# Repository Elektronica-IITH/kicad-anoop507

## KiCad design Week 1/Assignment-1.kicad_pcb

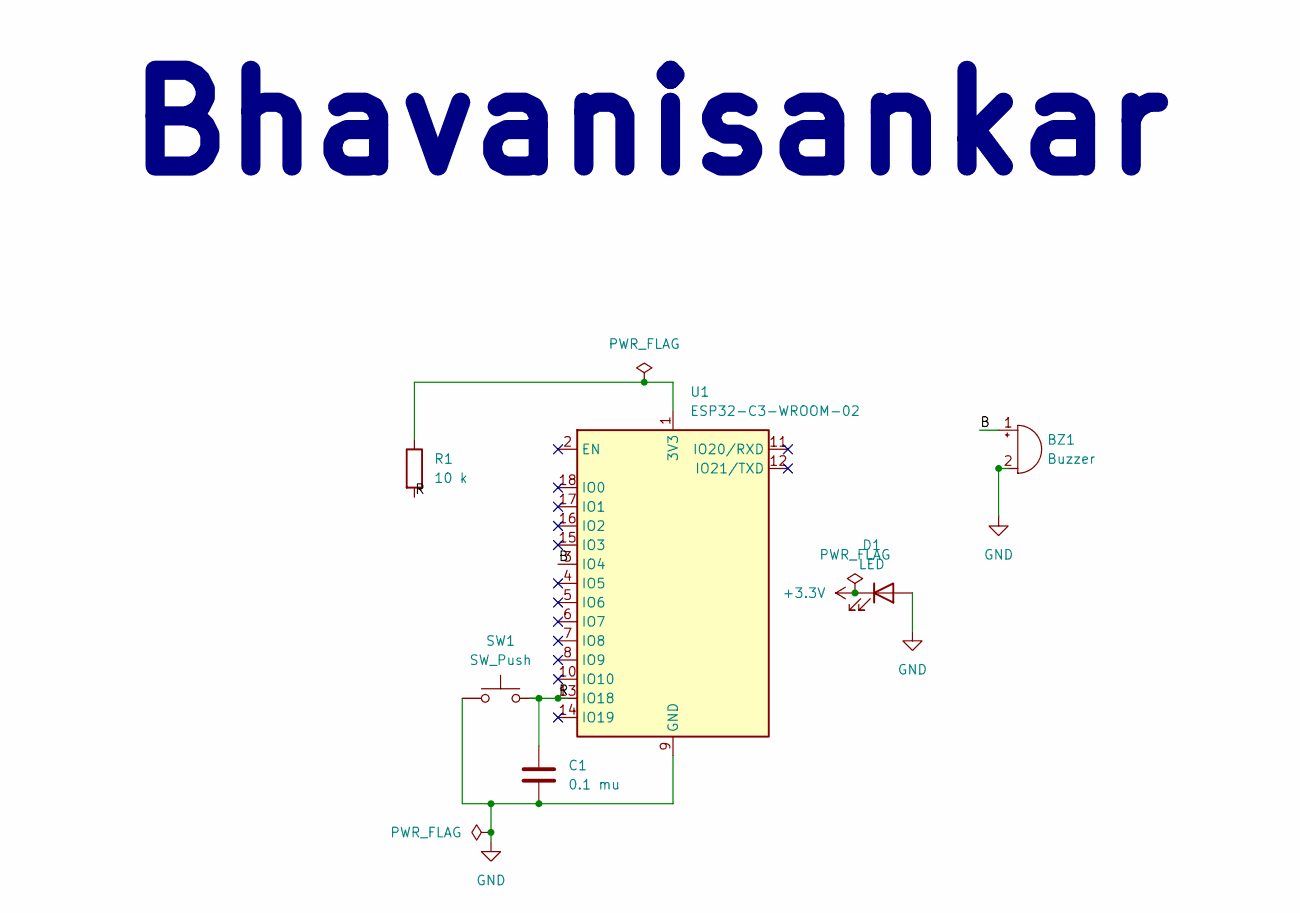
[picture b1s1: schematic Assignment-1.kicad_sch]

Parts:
BZ1: Buzzer; Buzzer_12x9.5RM7.6
C1: 0.1 mu; C_0201_0603Metric_Pad0.64x0.40mm_HandSolder
D1: LED; LED_1206_3216Metric_ReverseMount_Hole1.8x2.4mm
R1: 10 k; R_01005_0402Metric_Pad0.57x0.30mm_HandSolder
SW1: SW_Push; SW_PUSH_1P1T_6x3.5mm_H4.3_APEM_MJTP1243
U1: ESP32-C3-WROOM-02

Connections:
+3.3V: D1.1 (K)
/B: BZ1.1 (+), U1.3 (IO4)
/R: C1.1, R1.2, SW1.2, U1.13 (IO18)
GND: BZ1.2 (-), C1.2, D1.2 (A), SW1.1, U1.9 (GND), U1.19 (GND)
unnamed: R1.1, U1.1 (3V3)

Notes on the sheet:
Bhavanisankar

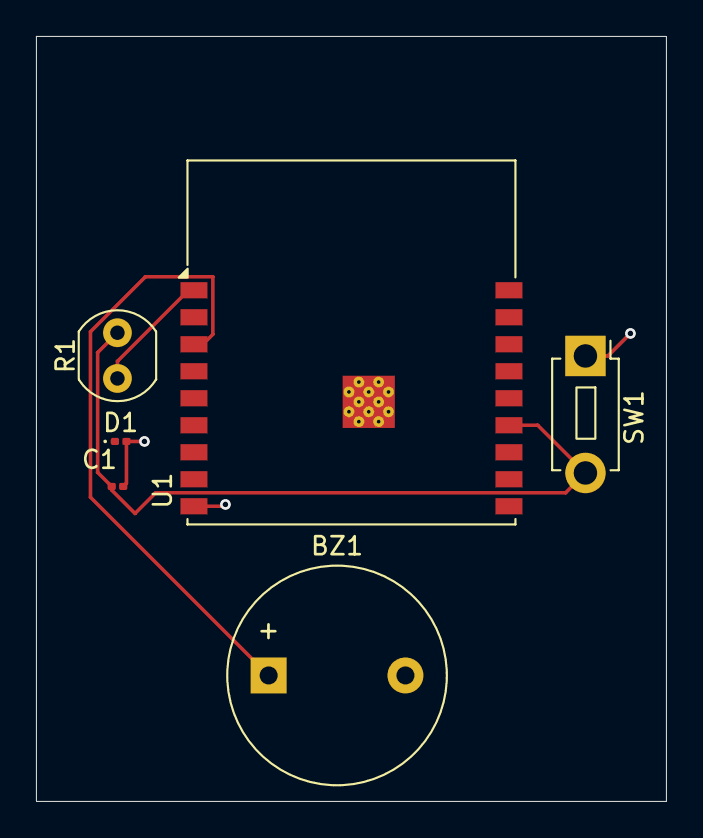
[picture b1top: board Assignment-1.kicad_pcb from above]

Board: 2 copper layers, 35.0 x 42.5 mm, 6 parts (0 on the bottom side), 4 nets.

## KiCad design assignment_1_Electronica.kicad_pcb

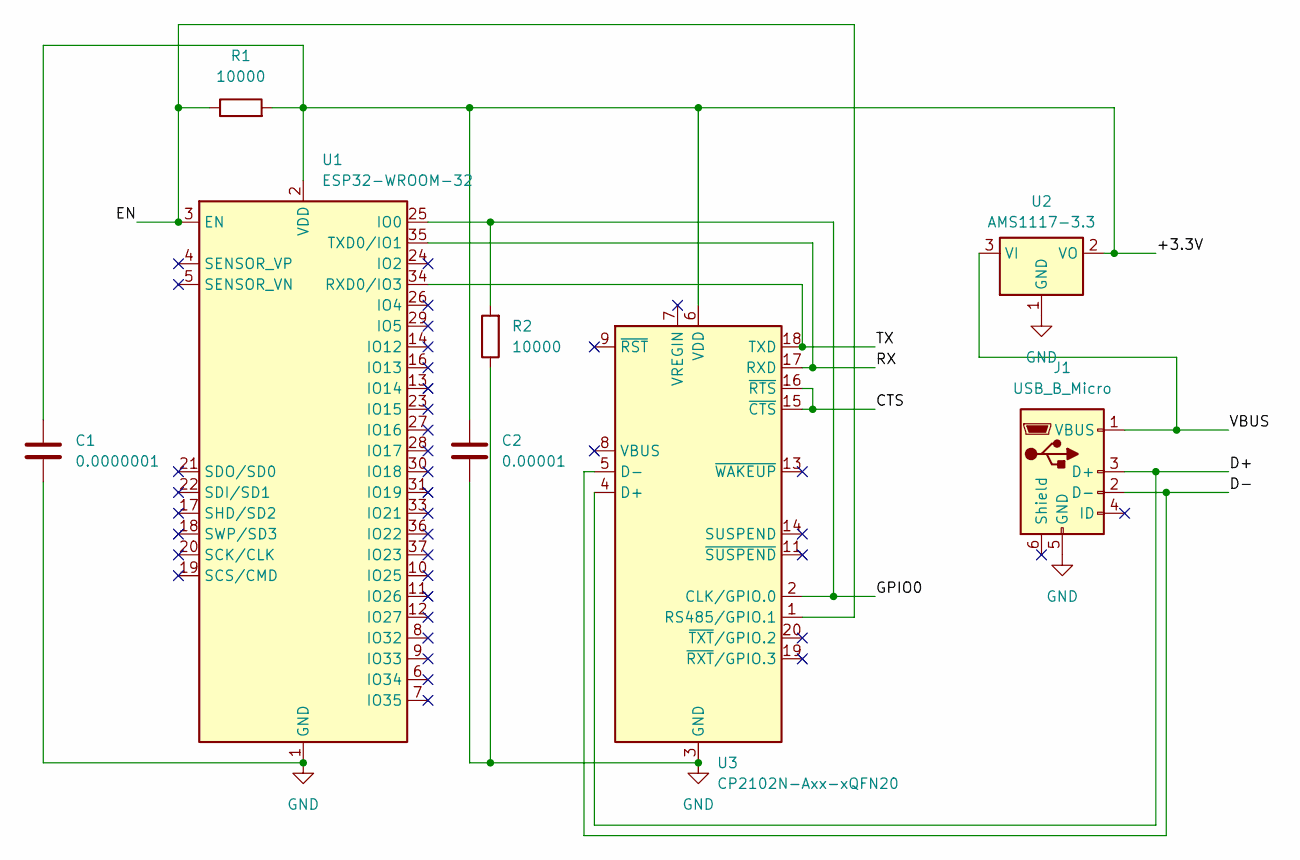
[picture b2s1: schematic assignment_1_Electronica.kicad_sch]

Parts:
C1: 0.0000001; C_Radial_D6.3mm_H11.0mm_P2.50mm
C2: 0.00001; C_Radial_D6.3mm_H11.0mm_P2.50mm
J1: USB_B_Micro; USB_Micro-B_Molex-105017-0001
R1, R2: 10000; R_Axial_DIN0204_L3.6mm_D1.6mm_P5.08mm_Vertical
U1: ESP32-WROOM-32
U2: AMS1117-3.3; SOT-223-3_TabPin2
U3: CP2102N-Axx-xQFN20; SiliconLabs_QFN-20-1EP_3x3mm_P0.5mm_EP1.8x1.8mm

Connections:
/+3.3V: C1.1, C2.1, R1.2, U1.2 (VDD), U2.2 (VO), U3.6 (VDD)
/CTS: U3.15 (~CTS), U3.16 (~RTS)
/D+: J1.3 (D+), U3.4 (D+)
/D-: J1.2 (D-), U3.5 (D-)
/EN: R1.1, U1.3 (EN), U3.1 (RS485/GPIO.1)
/GPIO0: R2.2, U1.25 (IO0), U3.2 (CLK/GPIO.0)
/RX: U1.35 (TXD0/IO1), U3.17 (RXD)
/TX: U1.34 (RXD0/IO3), U3.18 (TXD)
/VBUS: J1.1 (VBUS), U2.3 (VI)
GND: C1.2, C2.2, J1.5 (GND), R2.1, U1.1 (GND), U1.15 (GND), U1.38 (GND), U1.39 (GND), U2.1 (GND), U3.3 (GND), U3.12 (GND), U3.21 (GND)

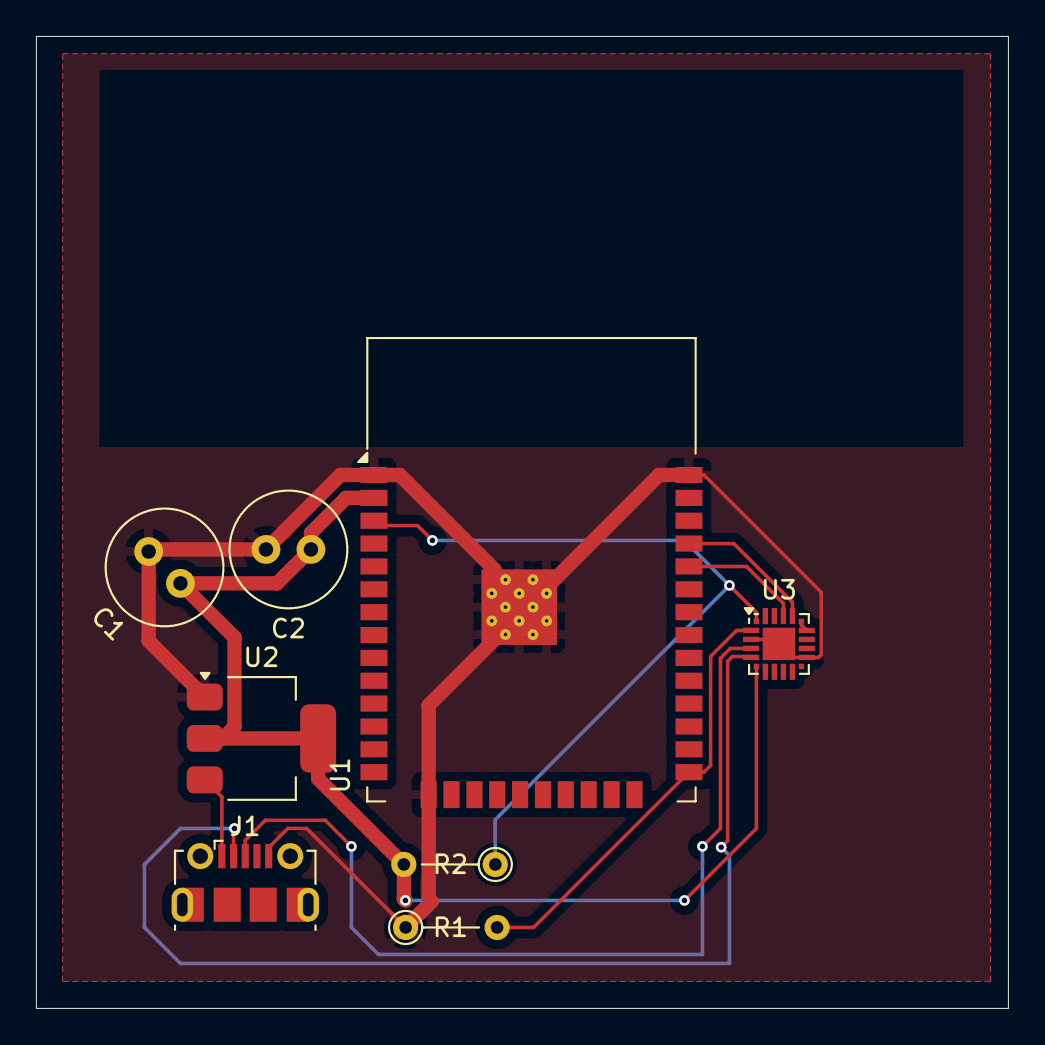
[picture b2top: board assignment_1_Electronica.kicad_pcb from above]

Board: 2 copper layers, 54.0 x 54.0 mm, 8 parts (0 on the bottom side), 10 nets.

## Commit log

2025-03-29 Automated PCB Check: Score 100/100
2025-03-29 Automated PCB Check: Score 0/100
2025-03-29 Assignment-1
    Electronika-1
2025-04-05 Assignment-2
